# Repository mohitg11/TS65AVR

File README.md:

# TS65 - AVR Based
The Split 65% Keyboard - AVR Based

This is a custom 65% style keyboard that is split in the middle to provide a more ergonomic option whilst not being drastically different from the standard stagger used on keyboards

#Features
- Open Source Design
- Fully Programmable Keys
- Split design for better ergonomics, while maintaining the currently "standard" keyboard layput
- PCBs and case designed so that the two sides can be aligned perfectly like a 65%, for others using the board, cleaner desk while not at it, etc.
- Multiple layers
- Alps/Cherry (PCB/Plate) switch support
- PCB mount stabs supported
- Backlight LED on top to maintain compatibility with the few backlit keysets out there
- 3 Indicator + CapsLock LED
- 18 SMD RGB LEDs on the bottom of the PCB for under/side glow
- SMD (SOD-123) diodes
- Individual resistors for the LEDs not required as it uses a dedicated LED driver
- Using large (0805) capacitors and resistors so it is easier to hand-solder

#Optional Features Supported
- Possibility to add a buzzer
- Possibility to add a PS/2 trackpoint to either halves.
- Possibility to add a rotary dial for changing volume, LED brightness, etc.

#Layout options
- Split backspace
- Split left shift
- ISO support
- Off-center capslock
- 2.75 and 1.75 right shift
- Lots of options for bottom row

In the below image you can see the different options available, the top four rows represent the four rows of th keyboard and the options for the final keyboard row is represented by the remaining rows in the image.

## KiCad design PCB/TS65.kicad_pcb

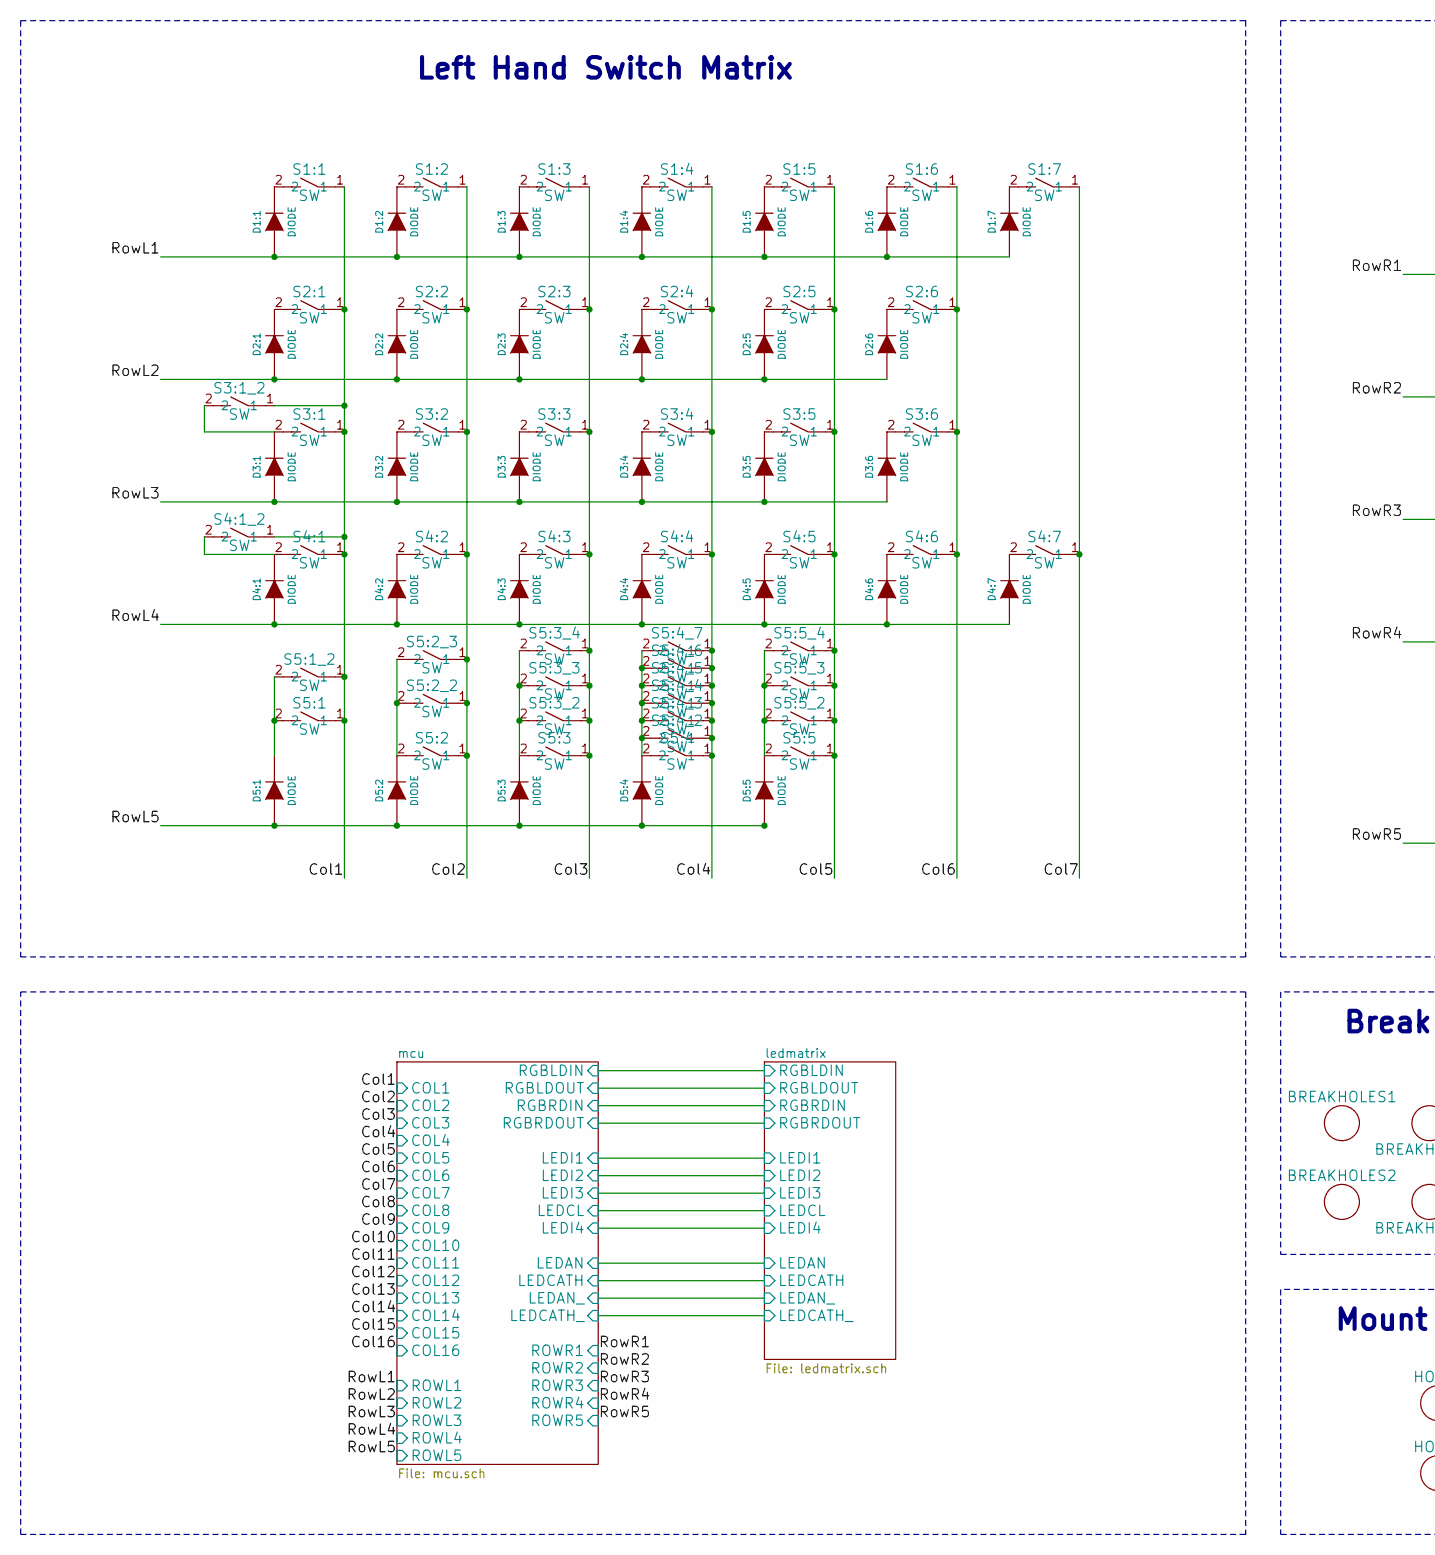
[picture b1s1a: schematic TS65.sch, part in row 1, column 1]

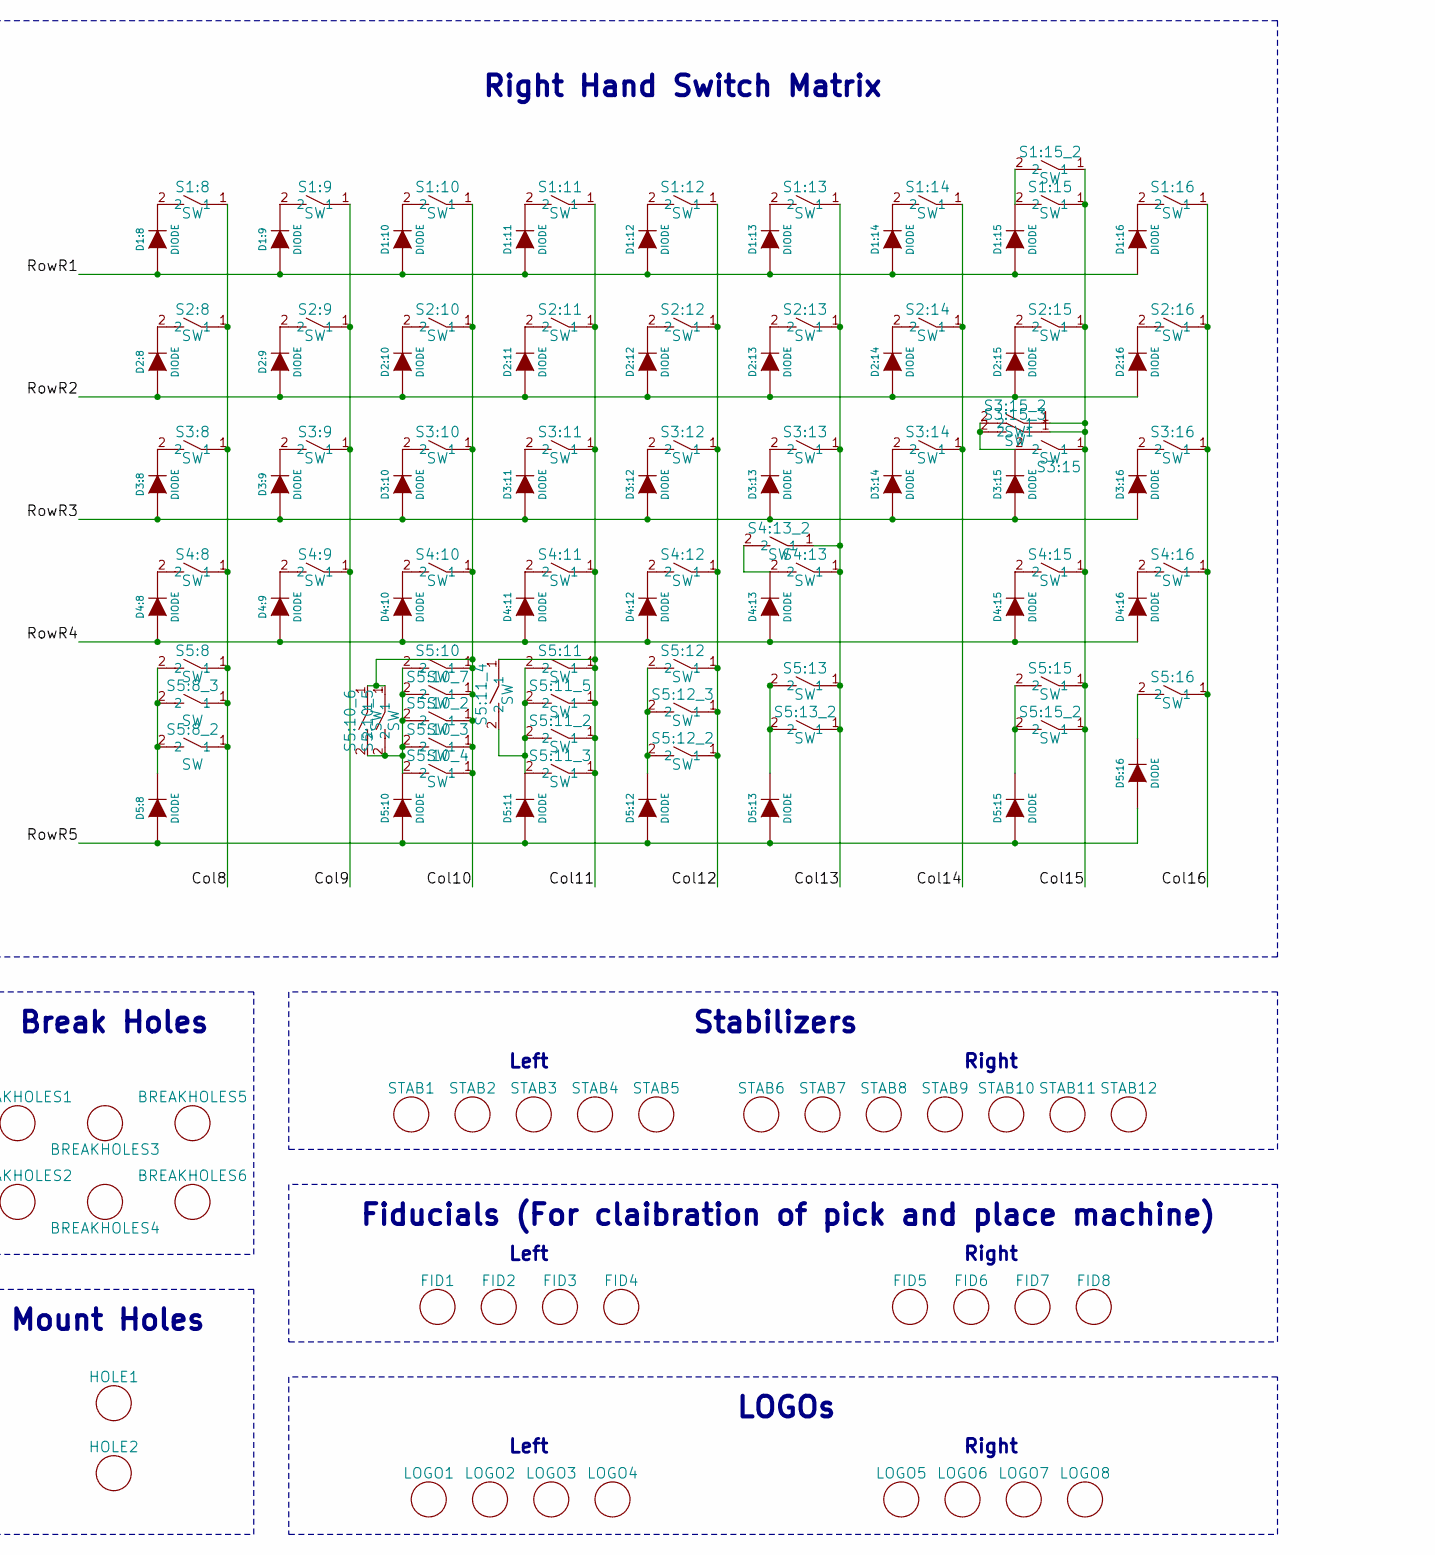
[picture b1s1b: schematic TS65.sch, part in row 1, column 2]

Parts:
BREAKHOLES1, BREAKHOLES2, BREAKHOLES3, BREAKHOLES4, BREAKHOLES5, BREAKHOLES6: MISC; BreakHoles
D1:1, D1:2, D1:3, D1:4, D1:5, D1:6, D1:7, D1:8, D1:9, D1:10, D1:11, D1:12, D1:13, D1:14, D1:15, D1:16, D2:1, D2:2, D2:3, D2:4, D2:5, D2:6, D2:8, D2:9, D2:10, D2:11, D2:12, D2:13, D2:14, D2:15, D2:16, D3:1, D3:2, D3:3, D3:4, D3:5, D3:6, D3:8, D3:9, D3:10, D3:11, D3:12, D3:13, D3:14, D3:15, D3:16, D4:1, D4:2, D4:3, D4:4, D4:5, D4:6, D4:7, D4:8, D4:9, D4:10, D4:11, D4:12, D4:13, D4:15, D4:16, D5:1, D5:2, D5:3, D5:4, D5:5, D5:8, D5:10, D5:11, D5:12, D5:13, D5:15, D5:16: DIODE; SOD123-DIODE
FID1, FID2, FID3, FID4, FID5, FID6, FID7, FID8: MISC; FID
HOLE1, HOLE2: MISC; FID
LOGO1, LOGO2, LOGO5, LOGO6: MISC; TS65-LOGO
LOGO3, LOGO4, LOGO7, LOGO8: MISC; OSHW
S1:1, S1:2, S1:3, S1:4, S1:5, S1:6, S1:7, S1:8, S1:9, S1:10, S1:11, S1:12, S1:13, S1:14, S1:15, S1:15_2, S1:16, S2:1, S2:2, S2:3, S2:4, S2:5, S2:6, S2:8, S2:9, S2:10, S2:11, S2:12, S2:13, S2:14, S2:15, S2:16, S3:1, S3:1_2, S3:2, S3:3, S3:4, S3:5, S3:6, S3:8, S3:9, S3:10, S3:11, S3:12, S3:13, S3:14, S3:15, S3:15_2, S3:15_3, S3:16, S4:1, S4:1_2, S4:2, S4:3, S4:4, S4:5, S4:6, S4:7, S4:8, S4:9, S4:10, S4:11, S4:12, S4:13, S4:13_2, S4:15, S4:16, S5:1, S5:1_2, S5:2, S5:2_2, S5:2_3, S5:3, S5:3_2, S5:3_3, S5:3_4, S5:4, S5:4_2, S5:4_3, S5:4_4, S5:4_5, S5:4_6, S5:4_7, S5:5, S5:5_2, S5:5_3, S5:5_4, S5:8, S5:8_2, S5:8_3, S5:10, S5:10_2, S5:10_3, S5:10_4, S5:10_5, S5:10_6, S5:10_7, S5:11, S5:11_2, S5:11_3, S5:11_4, S5:11_5, S5:12, S5:12_2, S5:12_3, S5:13, S5:13_2, S5:15, S5:15_2, S5:16: SW; MXALPS2
STAB1, STAB2, STAB3, STAB4, STAB5, STAB6, STAB7, STAB8, STAB9, STAB10, STAB11, STAB12: MISC; MX_200

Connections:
/Col1: S1:1.1, S2:1.1, S3:1.1, S3:1_2.1, S4:1.1, S4:1_2.1, S5:1.1, S5:1_2.1; also elsewhere on the board
/Col2: S1:2.1, S2:2.1, S3:2.1, S4:2.1, S5:2.1, S5:2_2.1, S5:2_3.1; also elsewhere on the board
/Col3: S1:3.1, S2:3.1, S3:3.1, S4:3.1, S5:3.1, S5:3_2.1, S5:3_3.1, S5:3_4.1; also elsewhere on the board
/Col4: S1:4.1, S2:4.1, S3:4.1, S4:4.1, S5:4.1, S5:4_2.1, S5:4_3.1, S5:4_4.1, S5:4_5.1, S5:4_6.1, S5:4_7.1; also elsewhere on the board
/Col5: S1:5.1, S2:5.1, S3:5.1, S4:5.1, S5:5.1, S5:5_2.1, S5:5_3.1, S5:5_4.1; also elsewhere on the board
/Col6: S1:6.1, S2:6.1, S3:6.1, S4:6.1; also elsewhere on the board
/Col7: S1:7.1, S4:7.1; also elsewhere on the board
/Col8: S1:8.1, S2:8.1, S3:8.1, S4:8.1, S5:8.1, S5:8_2.1, S5:8_3.1; also elsewhere on the board
/Col9: S1:9.1, S2:9.1, S3:9.1, S4:9.1; also elsewhere on the board
/Col10: S1:10.1, S2:10.1, S3:10.1, S4:10.1, S5:10.1, S5:10_2.1, S5:10_3.1, S5:10_4.1, S5:10_5.1, S5:10_6.1, S5:10_7.1; also elsewhere on the board
/Col11: S1:11.1, S2:11.1, S3:11.1, S4:11.1, S5:11.1, S5:11_2.1, S5:11_3.1, S5:11_4.1, S5:11_5.1; also elsewhere on the board
/Col12: S1:12.1, S2:12.1, S3:12.1, S4:12.1, S5:12.1, S5:12_2.1, S5:12_3.1; also elsewhere on the board
/Col13: S1:13.1, S2:13.1, S3:13.1, S4:13.1, S4:13_2.1, S5:13.1, S5:13_2.1; also elsewhere on the board
/Col14: S1:14.1, S2:14.1, S3:14.1; also elsewhere on the board
/Col15: S1:15.1, S1:15_2.1, S2:15.1, S3:15.1, S3:15_2.1, S3:15_3.1, S4:15.1, S5:15.1, S5:15_2.1; also elsewhere on the board
/Col16: S1:16.1, S2:16.1, S3:16.1, S4:16.1, S5:16.1; also elsewhere on the board
/RowL1: D1:1.1 (A), D1:2.1 (A), D1:3.1 (A), D1:4.1 (A), D1:5.1 (A), D1:6.1 (A), D1:7.1 (A); also elsewhere on the board
/RowL2: D2:1.1 (A), D2:2.1 (A), D2:3.1 (A), D2:4.1 (A), D2:5.1 (A), D2:6.1 (A); also elsewhere on the board
/RowL3: D3:1.1 (A), D3:2.1 (A), D3:3.1 (A), D3:4.1 (A), D3:5.1 (A), D3:6.1 (A); also elsewhere on the board
/RowL4: D4:1.1 (A), D4:2.1 (A), D4:3.1 (A), D4:4.1 (A), D4:5.1 (A), D4:6.1 (A), D4:7.1 (A); also elsewhere on the board
/RowL5: D5:1.1 (A), D5:2.1 (A), D5:3.1 (A), D5:4.1 (A), D5:5.1 (A); also elsewhere on the board
/RowR1: D1:8.1 (A), D1:9.1 (A), D1:10.1 (A), D1:11.1 (A), D1:12.1 (A), D1:13.1 (A), D1:14.1 (A), D1:15.1 (A), D1:16.1 (A); also elsewhere on the board
/RowR2: D2:8.1 (A), D2:9.1 (A), D2:10.1 (A), D2:11.1 (A), D2:12.1 (A), D2:13.1 (A), D2:14.1 (A), D2:15.1 (A), D2:16.1 (A); also elsewhere on the board
/RowR3: D3:8.1 (A), D3:9.1 (A), D3:10.1 (A), D3:11.1 (A), D3:12.1 (A), D3:13.1 (A), D3:14.1 (A), D3:15.1 (A), D3:16.1 (A); also elsewhere on the board
/RowR4: D4:8.1 (A), D4:9.1 (A), D4:10.1 (A), D4:11.1 (A), D4:12.1 (A), D4:13.1 (A), D4:15.1 (A), D4:16.1 (A); also elsewhere on the board
/RowR5: D5:8.1 (A), D5:10.1 (A), D5:11.1 (A), D5:12.1 (A), D5:13.1 (A), D5:15.1 (A), D5:16.1 (A); also elsewhere on the board
unnamed: D1:1.2 (K), S1:1.2
unnamed: D1:2.2 (K), S1:2.2
unnamed: D1:3.2 (K), S1:3.2
unnamed: D1:4.2 (K), S1:4.2
unnamed: D1:5.2 (K), S1:5.2
unnamed: D1:6.2 (K), S1:6.2
unnamed: D1:7.2 (K), S1:7.2
unnamed: D1:8.2 (K), S1:8.2
unnamed: D1:9.2 (K), S1:9.2
unnamed: D1:10.2 (K), S1:10.2
unnamed: D1:11.2 (K), S1:11.2
unnamed: D1:12.2 (K), S1:12.2
unnamed: D1:13.2 (K), S1:13.2
unnamed: D1:14.2 (K), S1:14.2
unnamed: D1:15.2 (K), S1:15.2, S1:15_2.2
unnamed: D1:16.2 (K), S1:16.2
unnamed: D2:1.2 (K), S2:1.2
unnamed: D2:2.2 (K), S2:2.2
unnamed: D2:3.2 (K), S2:3.2
unnamed: D2:4.2 (K), S2:4.2
unnamed: D2:5.2 (K), S2:5.2
unnamed: D2:6.2 (K), S2:6.2
unnamed: D2:8.2 (K), S2:8.2
unnamed: D2:9.2 (K), S2:9.2
unnamed: D2:10.2 (K), S2:10.2
unnamed: D2:11.2 (K), S2:11.2
unnamed: D2:12.2 (K), S2:12.2
unnamed: D2:13.2 (K), S2:13.2
unnamed: D2:14.2 (K), S2:14.2
unnamed: D2:15.2 (K), S2:15.2
unnamed: D2:16.2 (K), S2:16.2
unnamed: D3:1.2 (K), S3:1.2, S3:1_2.2
unnamed: D3:2.2 (K), S3:2.2
unnamed: D3:3.2 (K), S3:3.2
unnamed: D3:4.2 (K), S3:4.2
unnamed: D3:5.2 (K), S3:5.2
unnamed: D3:6.2 (K), S3:6.2
unnamed: D3:8.2 (K), S3:8.2
unnamed: D3:9.2 (K), S3:9.2
unnamed: D3:10.2 (K), S3:10.2
unnamed: D3:11.2 (K), S3:11.2
unnamed: D3:12.2 (K), S3:12.2
unnamed: D3:13.2 (K), S3:13.2
unnamed: D3:14.2 (K), S3:14.2
unnamed: D3:15.2 (K), S3:15.2, S3:15_2.2, S3:15_3.2
unnamed: D3:16.2 (K), S3:16.2
unnamed: D4:1.2 (K), S4:1.2, S4:1_2.2
unnamed: D4:2.2 (K), S4:2.2
unnamed: D4:3.2 (K), S4:3.2
unnamed: D4:4.2 (K), S4:4.2
unnamed: D4:5.2 (K), S4:5.2
unnamed: D4:6.2 (K), S4:6.2
unnamed: D4:7.2 (K), S4:7.2
unnamed: D4:8.2 (K), S4:8.2
unnamed: D4:9.2 (K), S4:9.2
unnamed: D4:10.2 (K), S4:10.2
unnamed: D4:11.2 (K), S4:11.2
unnamed: D4:12.2 (K), S4:12.2
unnamed: D4:13.2 (K), S4:13.2, S4:13_2.2
unnamed: D4:15.2 (K), S4:15.2
unnamed: D4:16.2 (K), S4:16.2
unnamed: D5:1.2 (K), S5:1.2, S5:1_2.2
unnamed: D5:2.2 (K), S5:2.2, S5:2_2.2, S5:2_3.2
unnamed: D5:3.2 (K), S5:3.2, S5:3_2.2, S5:3_3.2, S5:3_4.2
unnamed: D5:4.2 (K), S5:4.2, S5:4_2.2, S5:4_3.2, S5:4_4.2, S5:4_5.2, S5:4_6.2, S5:4_7.2
unnamed: D5:5.2 (K), S5:5.2, S5:5_2.2, S5:5_3.2, S5:5_4.2
unnamed: D5:8.2 (K), S5:8.2, S5:8_2.2, S5:8_3.2
unnamed: D5:10.2 (K), S5:10.2, S5:10_2.2, S5:10_3.2, S5:10_4.2, S5:10_5.2, S5:10_6.2, S5:10_7.2
unnamed: D5:11.2 (K), S5:11.2, S5:11_2.2, S5:11_3.2, S5:11_4.2, S5:11_5.2
unnamed: D5:12.2 (K), S5:12.2, S5:12_2.2, S5:12_3.2
unnamed: D5:13.2 (K), S5:13.2, S5:13_2.2
unnamed: D5:15.2 (K), S5:15.2, S5:15_2.2
unnamed: D5:16.2 (K), S5:16.2

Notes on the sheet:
Left Hand Switch Matrix
Right Hand Switch Matrix
Right
Left
Stabilizers
Fiducials (For claibration of pick and place machine)
LOGOs
Break Holes
Mount Holes

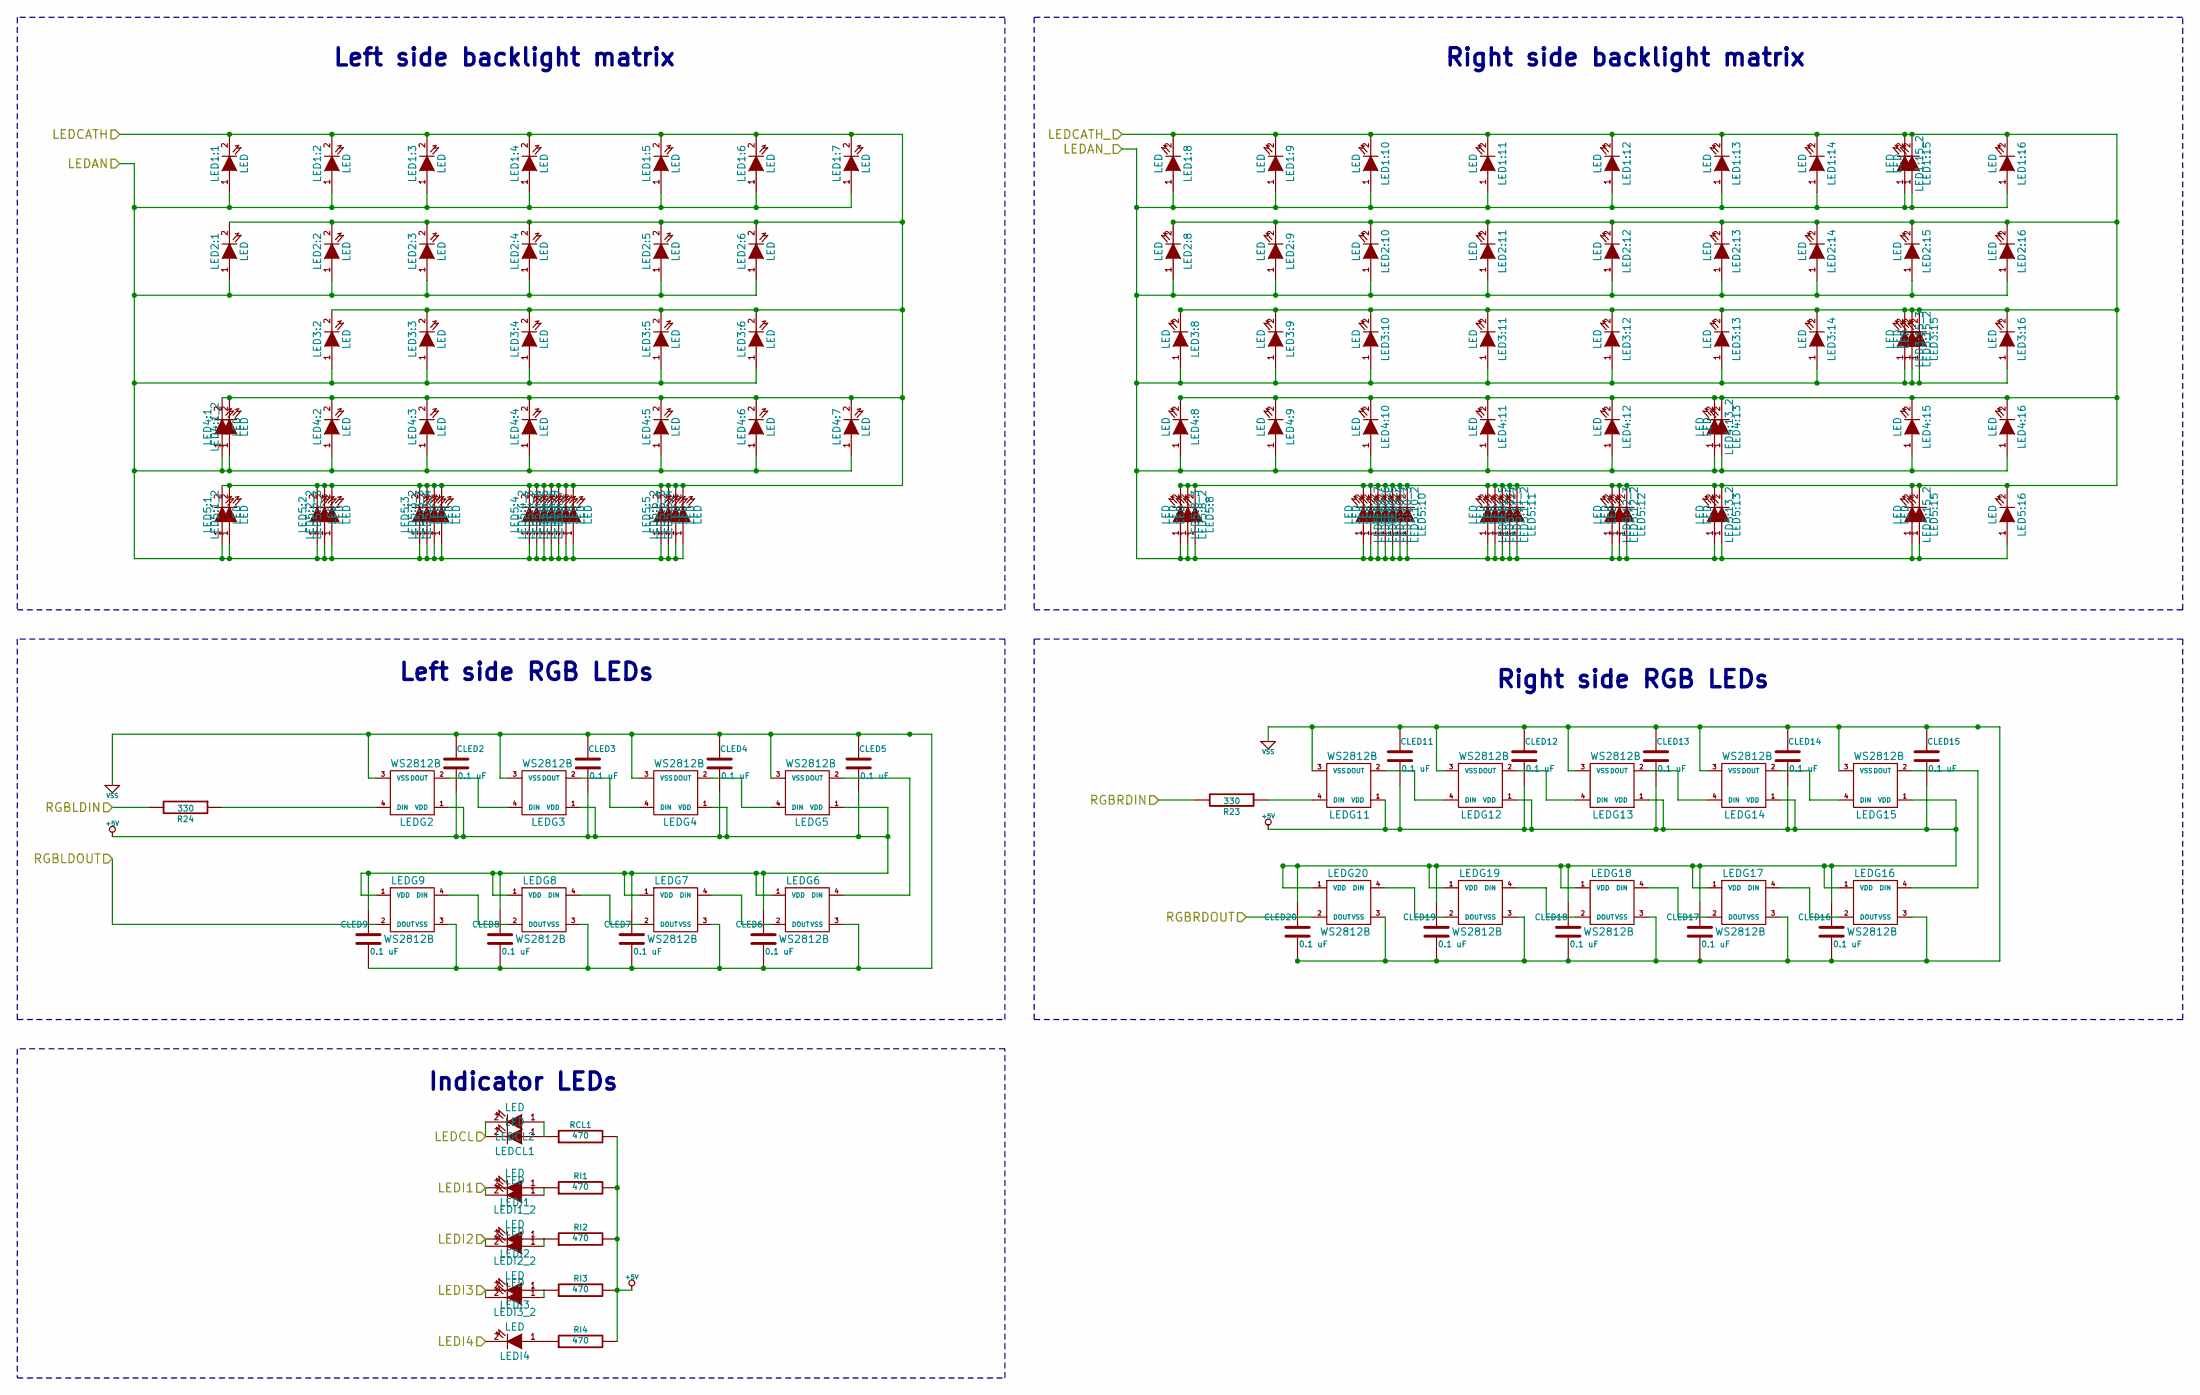
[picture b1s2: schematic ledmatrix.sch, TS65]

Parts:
CLED2, CLED3, CLED4, CLED5, CLED6, CLED7, CLED8, CLED9, CLED11, CLED12, CLED13, CLED14, CLED15, CLED16, CLED17, CLED18, CLED19, CLED20: 0.1 uF; SMD_0805
LED1:1, LED1:2, LED1:3, LED1:4, LED1:5, LED1:6, LED1:7, LED1:8, LED1:9, LED1:10, LED1:11, LED1:12, LED1:13, LED1:14, LED1:15, LED1:15_2, LED1:16, LED2:1, LED2:2, LED2:3, LED2:4, LED2:5, LED2:6, LED2:8, LED2:9, LED2:10, LED2:11, LED2:12, LED2:13, LED2:14, LED2:15, LED2:16, LED3:2, LED3:3, LED3:4, LED3:5, LED3:6, LED3:8, LED3:9, LED3:10, LED3:11, LED3:12, LED3:13, LED3:14, LED3:15, LED3:15_2, LED3:15_3, LED3:16, LED4:1, LED4:1_2, LED4:2, LED4:3, LED4:4, LED4:5, LED4:6, LED4:7, LED4:8, LED4:9, LED4:10, LED4:11, LED4:12, LED4:13, LED4:13_2, LED4:15, LED4:16, LED5:1, LED5:1_2, LED5:2, LED5:2_2, LED5:2_3, LED5:3, LED5:3_2, LED5:3_3, LED5:3_4, LED5:4, LED5:4_2, LED5:4_3, LED5:4_4, LED5:4_5, LED5:4_6, LED5:4_7, LED5:5, LED5:5_2, LED5:5_3, LED5:5_4, LED5:8, LED5:8_2, LED5:8_3, LED5:10, LED5:10_2, LED5:10_3, LED5:10_4, LED5:10_5, LED5:10_6, LED5:10_7, LED5:11, LED5:11_2, LED5:11_3, LED5:11_4, LED5:11_5, LED5:12, LED5:12_2, LED5:12_3, LED5:13, LED5:13_2, LED5:15, LED5:15_2, LED5:16: LED; INSW_LEDS_REG
LEDCL1, LEDCL2: LED; INSW_LEDS_REG
LEDG2, LEDG3, LEDG4, LEDG5, LEDG6, LEDG7, LEDG8, LEDG9, LEDG11, LEDG12, LEDG13, LEDG14, LEDG15, LEDG16, LEDG17, LEDG18, LEDG19, LEDG20: WS2812B
LEDI1, LEDI1_2, LEDI2, LEDI2_2, LEDI3, LEDI3_2: LED; LED-3MM
LEDI4: LED; LED_0805
R23, R24: 330; SMD_0805
RCL1: 470; SMD_0805
RI1, RI2, RI3, RI4: 470; SMD_0805

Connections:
+5V: CLED2.2, CLED3.2, CLED4.2, CLED5.2, CLED6.1, CLED7.1, CLED8.1, CLED9.1, CLED11.2, CLED12.2, CLED13.2, CLED14.2, CLED15.2, CLED16.1, CLED17.1, CLED18.1, CLED19.1, CLED20.1, LEDG2.1 (VDD), LEDG3.1 (VDD), LEDG4.1 (VDD), LEDG5.1 (VDD), LEDG6.1 (VDD), LEDG7.1 (VDD), LEDG8.1 (VDD), LEDG9.1 (VDD), LEDG11.1 (VDD), LEDG12.1 (VDD), LEDG13.1 (VDD), LEDG14.1 (VDD), LEDG15.1 (VDD), LEDG16.1 (VDD), LEDG17.1 (VDD), LEDG18.1 (VDD), LEDG19.1 (VDD), LEDG20.1 (VDD), RCL1.2, RI1.2, RI2.2, RI3.2, RI4.2; also elsewhere on the board
/ledmatrix/LEDAN_: LED1:8.1 (A), LED1:9.1 (A), LED1:10.1 (A), LED1:11.1 (A), LED1:12.1 (A), LED1:13.1 (A), LED1:14.1 (A), LED1:15.1 (A), LED1:15_2.1 (A), LED1:16.1 (A), LED2:8.1 (A), LED2:9.1 (A), LED2:10.1 (A), LED2:11.1 (A), LED2:12.1 (A), LED2:13.1 (A), LED2:14.1 (A), LED2:15.1 (A), LED2:16.1 (A), LED3:8.1 (A), LED3:9.1 (A), LED3:10.1 (A), LED3:11.1 (A), LED3:12.1 (A), LED3:13.1 (A), LED3:14.1 (A), LED3:15.1 (A), LED3:15_2.1 (A), LED3:15_3.1 (A), LED3:16.1 (A), LED4:8.1 (A), LED4:9.1 (A), LED4:10.1 (A), LED4:11.1 (A), LED4:12.1 (A), LED4:13.1 (A), LED4:13_2.1 (A), LED4:15.1 (A), LED4:16.1 (A), LED5:8.1 (A), LED5:8_2.1 (A), LED5:8_3.1 (A), LED5:10.1 (A), LED5:10_2.1 (A), LED5:10_3.1 (A), LED5:10_4.1 (A), LED5:10_5.1 (A), LED5:10_6.1 (A), LED5:10_7.1 (A), LED5:11.1 (A), LED5:11_2.1 (A), LED5:11_3.1 (A), LED5:11_4.1 (A), LED5:11_5.1 (A), LED5:12.1 (A), LED5:12_2.1 (A), LED5:12_3.1 (A), LED5:13.1 (A), LED5:13_2.1 (A), LED5:15.1 (A), LED5:15_2.1 (A), LED5:16.1 (A); also elsewhere on the board
/ledmatrix/LEDCATH_: LED1:8.2 (K), LED1:9.2 (K), LED1:10.2 (K), LED1:11.2 (K), LED1:12.2 (K), LED1:13.2 (K), LED1:14.2 (K), LED1:15.2 (K), LED1:15_2.2 (K), LED1:16.2 (K), LED2:8.2 (K), LED2:9.2 (K), LED2:10.2 (K), LED2:11.2 (K), LED2:12.2 (K), LED2:13.2 (K), LED2:14.2 (K), LED2:15.2 (K), LED2:16.2 (K), LED3:8.2 (K), LED3:9.2 (K), LED3:10.2 (K), LED3:11.2 (K), LED3:12.2 (K), LED3:13.2 (K), LED3:14.2 (K), LED3:15.2 (K), LED3:15_2.2 (K), LED3:15_3.2 (K), LED3:16.2 (K), LED4:8.2 (K), LED4:9.2 (K), LED4:10.2 (K), LED4:11.2 (K), LED4:12.2 (K), LED4:13.2 (K), LED4:13_2.2 (K), LED4:15.2 (K), LED4:16.2 (K), LED5:8.2 (K), LED5:8_2.2 (K), LED5:8_3.2 (K), LED5:10.2 (K), LED5:10_2.2 (K), LED5:10_3.2 (K), LED5:10_4.2 (K), LED5:10_5.2 (K), LED5:10_6.2 (K), LED5:10_7.2 (K), LED5:11.2 (K), LED5:11_2.2 (K), LED5:11_3.2 (K), LED5:11_4.2 (K), LED5:11_5.2 (K), LED5:12.2 (K), LED5:12_2.2 (K), LED5:12_3.2 (K), LED5:13.2 (K), LED5:13_2.2 (K), LED5:15.2 (K), LED5:15_2.2 (K), LED5:16.2 (K); also elsewhere on the board
/ledmatrix/LEDCL: LEDCL1.2 (K), LEDCL2.2 (K); also elsewhere on the board
/ledmatrix/LEDI1: LEDI1.2 (K), LEDI1_2.2 (K); also elsewhere on the board
/ledmatrix/LEDI2: LEDI2.2 (K), LEDI2_2.2 (K); also elsewhere on the board
/ledmatrix/LEDI3: LEDI3.2 (K), LEDI3_2.2 (K); also elsewhere on the board
/ledmatrix/LEDI4: LEDI4.2 (K); also elsewhere on the board
/ledmatrix/RGBLDIN: R24.2; also elsewhere on the board
/ledmatrix/RGBRDIN: R23.2; also elsewhere on the board
/ledmatrix/RGBRDOUT: LEDG20.2 (DOUT); also elsewhere on the board
unnamed: LEDCL1.1 (A), LEDCL2.1 (A), RCL1.1
unnamed: LEDG2.2 (DOUT), LEDG3.4 (DIN)
unnamed: LEDG2.4 (DIN), R24.1
unnamed: LEDG3.2 (DOUT), LEDG4.4 (DIN)
unnamed: LEDG4.2 (DOUT), LEDG5.4 (DIN)
unnamed: LEDG5.2 (DOUT), LEDG6.4 (DIN)
unnamed: LEDG6.2 (DOUT), LEDG7.4 (DIN)
unnamed: LEDG7.2 (DOUT), LEDG8.4 (DIN)
unnamed: LEDG8.2 (DOUT), LEDG9.4 (DIN)
unnamed: LEDG11.2 (DOUT), LEDG12.4 (DIN)
unnamed: LEDG11.4 (DIN), R23.1
unnamed: LEDG12.2 (DOUT), LEDG13.4 (DIN)
unnamed: LEDG13.2 (DOUT), LEDG14.4 (DIN)
unnamed: LEDG14.2 (DOUT), LEDG15.4 (DIN)
unnamed: LEDG15.2 (DOUT), LEDG16.4 (DIN)
unnamed: LEDG16.2 (DOUT), LEDG17.4 (DIN)
unnamed: LEDG17.2 (DOUT), LEDG18.4 (DIN)
unnamed: LEDG18.2 (DOUT), LEDG19.4 (DIN)
unnamed: LEDG19.2 (DOUT), LEDG20.4 (DIN)
unnamed: LEDI1.1 (A), LEDI1_2.1 (A), RI1.1
unnamed: LEDI2.1 (A), LEDI2_2.1 (A), RI2.1
unnamed: LEDI3.1 (A), LEDI3_2.1 (A), RI3.1
unnamed: LEDI4.1 (A), RI4.1
VSS: CLED2.1, CLED3.1, CLED4.1, CLED5.1, CLED6.2, CLED7.2, CLED8.2, CLED9.2, CLED11.1, CLED12.1, CLED13.1, CLED14.1, CLED15.1, CLED16.2, CLED17.2, CLED18.2, CLED19.2, CLED20.2, LEDG2.3 (VSS), LEDG3.3 (VSS), LEDG4.3 (VSS), LEDG5.3 (VSS), LEDG6.3 (VSS), LEDG7.3 (VSS), LEDG8.3 (VSS), LEDG9.3 (VSS), LEDG11.3 (VSS), LEDG12.3 (VSS), LEDG13.3 (VSS), LEDG14.3 (VSS), LEDG15.3 (VSS), LEDG16.3 (VSS), LEDG17.3 (VSS), LEDG18.3 (VSS), LEDG19.3 (VSS), LEDG20.3 (VSS); also elsewhere on the board

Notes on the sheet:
Left side backlight matrix
Right side backlight matrix
Right side RGB LEDs
Left side RGB LEDs
Indicator LEDs
